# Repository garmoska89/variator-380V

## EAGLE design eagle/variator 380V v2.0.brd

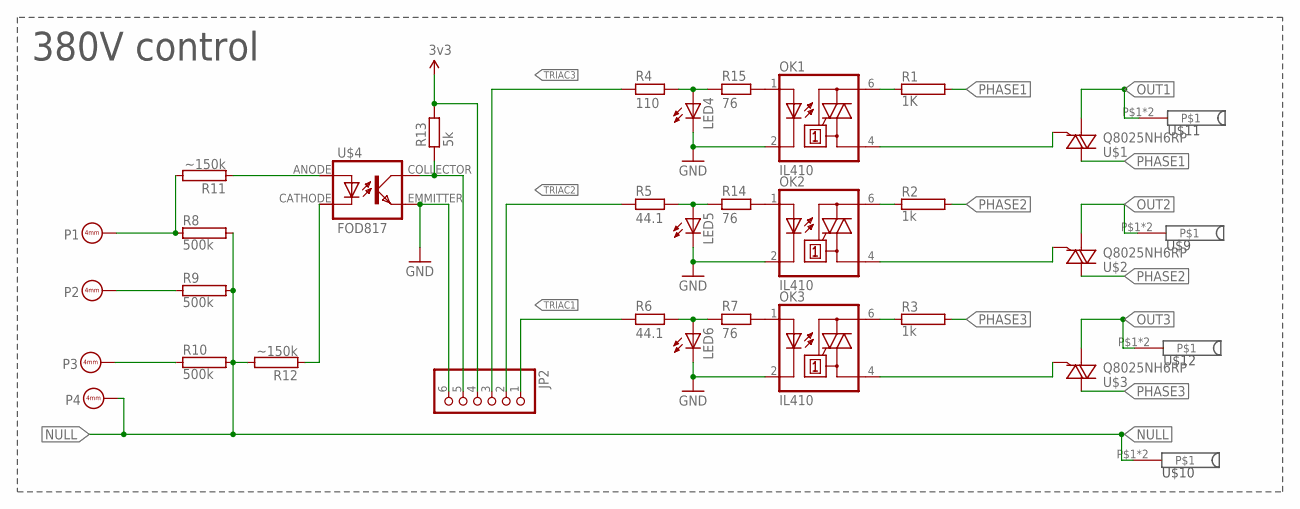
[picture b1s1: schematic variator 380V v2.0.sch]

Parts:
JP2: PINHD-1X6/90; 1X06/90
LED4, LED5, LED6: LED5MM
OK1, OK2, OK3: IL410; DIL06
P1, P2, P3, P4: BANANA
R1: 1K; HPS58
R2, R3: 1k; HPS58
R4: 110; 1206
R5, R6: 44.1; 1206
R7, R14, R15: 76; 1206
R8, R9, R10: 500k; HPS58
R11, R12: ~150k; HPS58
R13: 5k; 1206
U$1, U$2, U$3: Q8025NH6RP; TO-263
U$4: FOD817; FOD_4PIN
U$9, U$10, U$11, U$12: BANANA

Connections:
3V3: JP2.4, R13.2
GND: JP2.6, LED4.K (C), LED5.K (C), LED6.K (C), OK1.2 (C), OK2.2 (C), OK3.2 (C), U$4.EMMITTER (EMIT)
unnamed: OK2.4 (A1), U$2.G
unnamed: OK1.4 (A1), U$1.G
unnamed: OK3.4 (A1), U$3.G
unnamed: OK1.6 (A2), R1.1
unnamed: OK2.6 (A2), R2.1
unnamed: OK3.6 (A2), R3.1
unnamed: LED4.A, R4.2, R15.1
unnamed: OK3.1 (A), R7.2
unnamed: OK2.1 (A), R14.2
unnamed: LED5.A, R5.2, R14.1
unnamed: LED6.A, R6.2, R7.1
unnamed: OK1.1 (A), R15.2
unnamed: R12.1, U$4.CATHODE
unnamed: R11.1, U$4.ANODE
unnamed: JP2.5, R13.1, U$4.COLLECTOR (COL)
NULL: P4.P$1, R8.2, R9.2, R10.2, R12.2, U$10.P$1, U$10.P$2
OUT1: U$1.T1, U$11.P$1, U$11.P$2
OUT2: U$2.T1, U$9.P$1, U$9.P$2
OUT3: U$3.T1, U$12.P$1, U$12.P$2
PHASE1: P1.P$1, R1.2, R8.1, R11.2, U$1.T2
PHASE2: P2.P$1, R2.2, R9.1, U$2.T2
PHASE3: P3.P$1, R3.2, R10.1, U$3.T2
TRIAC1: JP2.1, R6.1
TRIAC2: JP2.2, R5.1
TRIAC3: JP2.3, R4.1

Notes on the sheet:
380V control

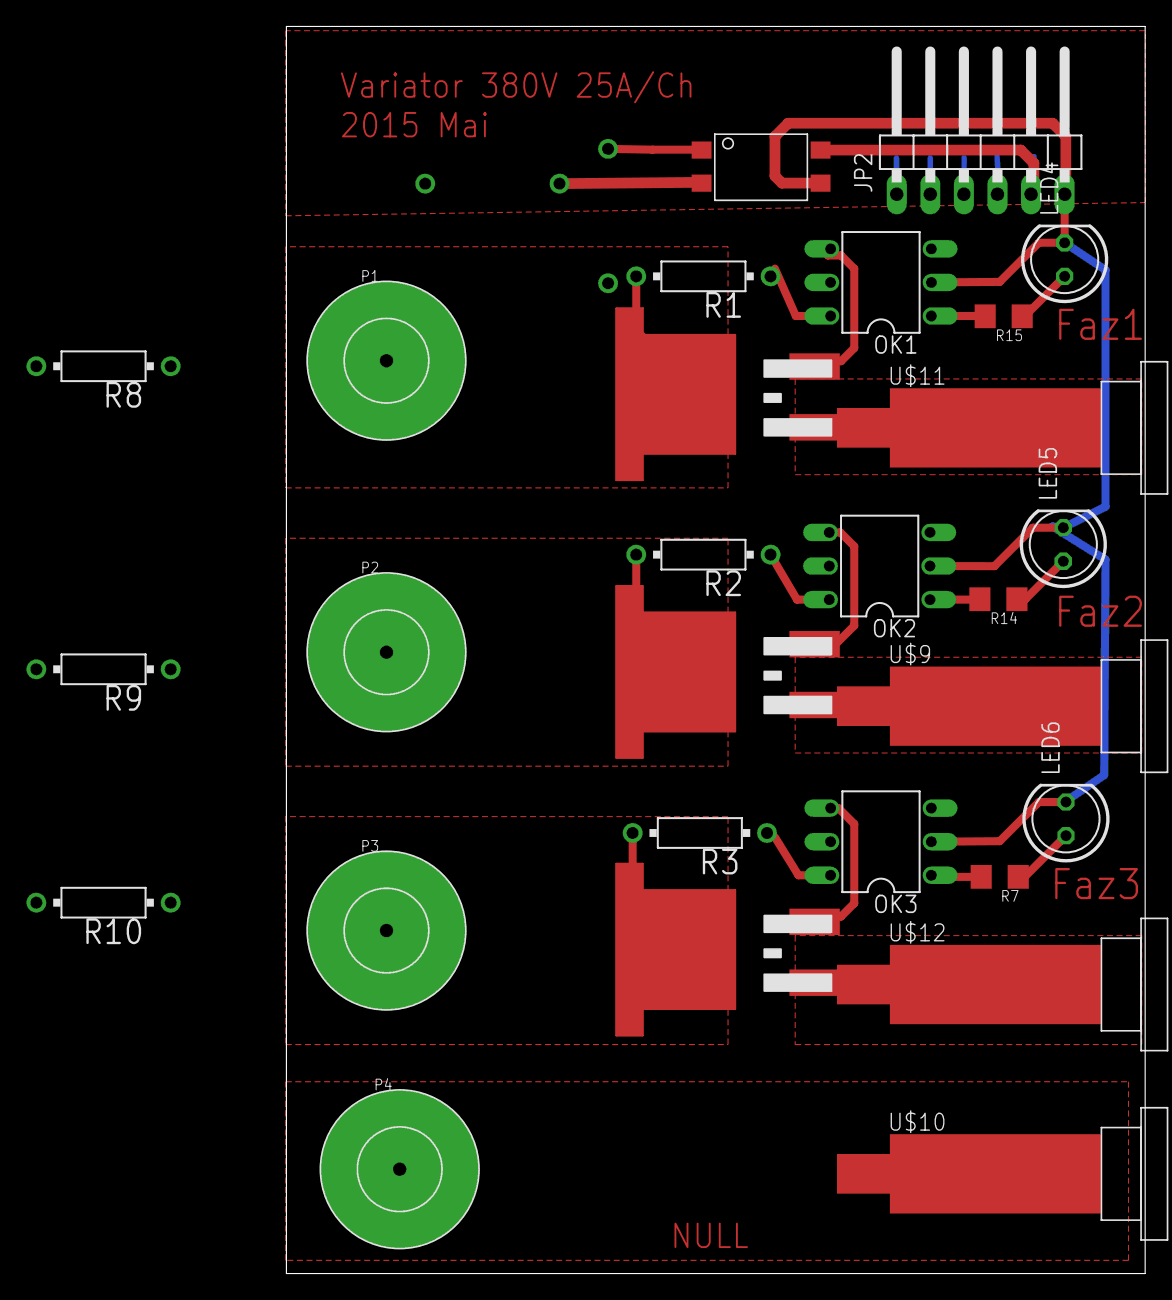
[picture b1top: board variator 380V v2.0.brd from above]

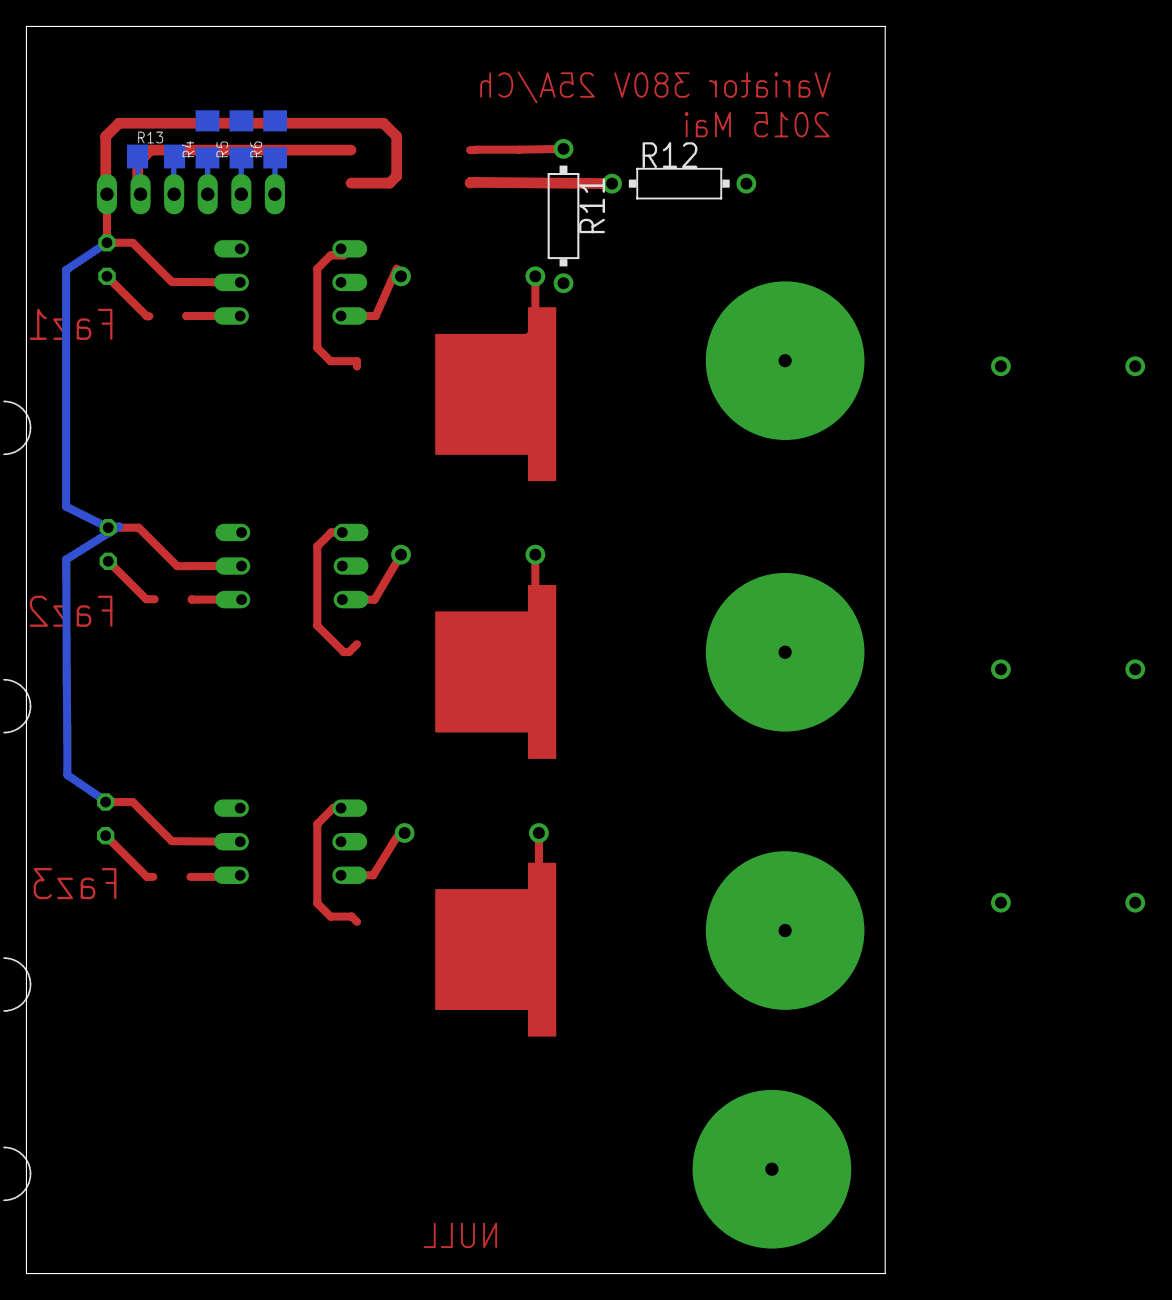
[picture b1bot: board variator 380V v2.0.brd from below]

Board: 2 copper layers, 65.0 x 94.3 mm, 34 parts (6 on the bottom side), 27 nets.

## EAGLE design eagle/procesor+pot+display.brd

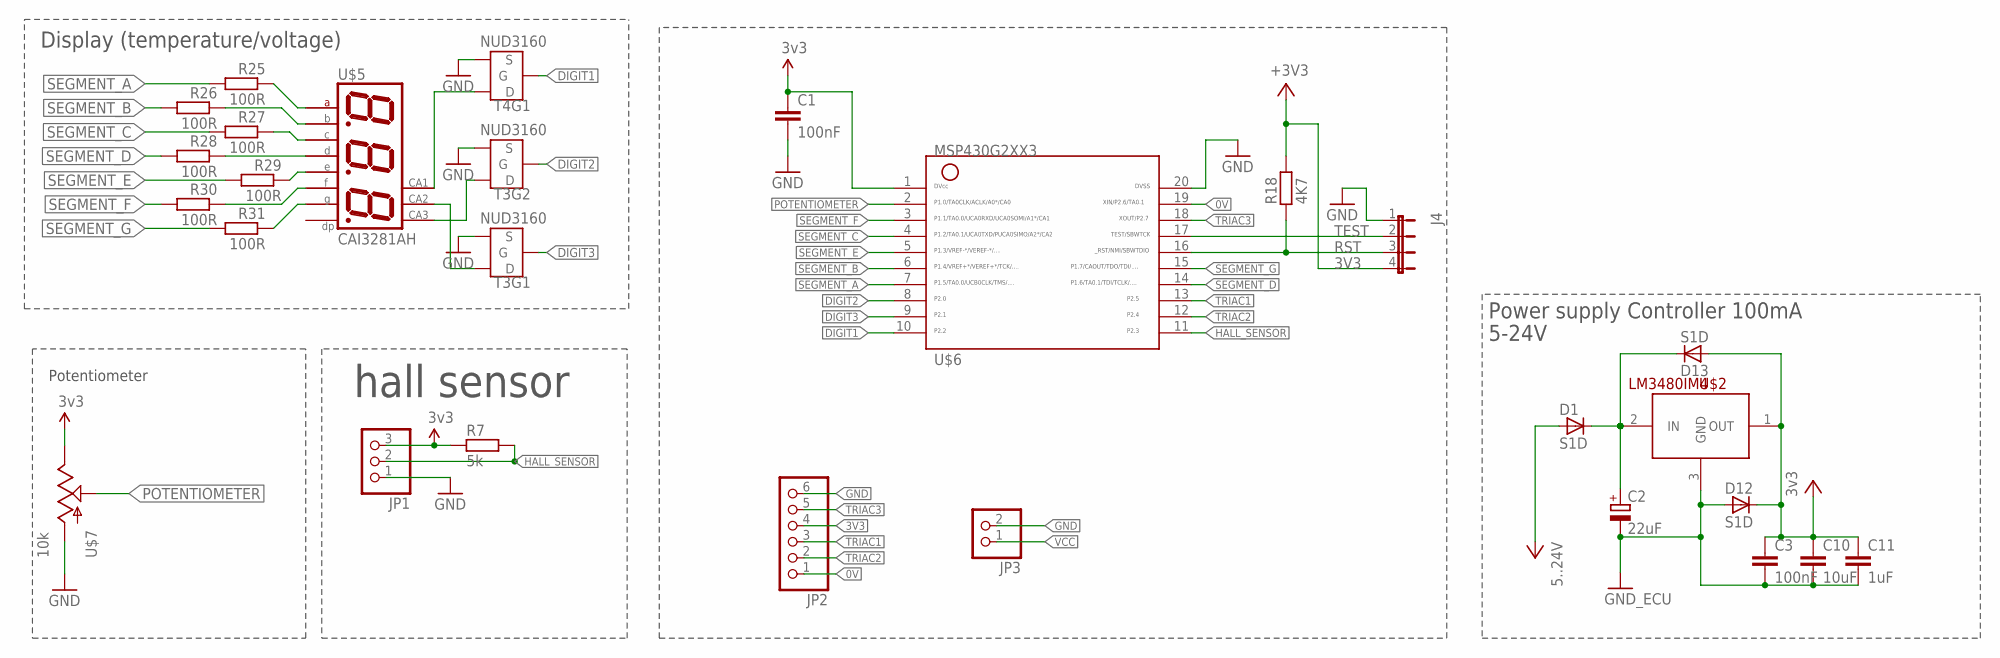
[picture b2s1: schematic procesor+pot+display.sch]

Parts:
C1: 100nF; 0603
C2: 22uF; C_EL_6.3X5.4
C3: 100nF; 1206
C10: 10uF; 1206
C11: 1uF; 1206
D1, D12, D13: S1D
J4: JP4
JP1: PINHD-1X3; 1X03
JP2: PINHD-1X6/90; 1X06/90
JP3: PINHD-1X2/90; 1X02/90
R7: 5k; 0603
R18: 4K7; 0805
R25, R26, R27, R28, R29, R30, R31: 100R; R0603
T3, T4: NUD3160; SOT23-6
U$2: LM3480IM4; SOT23-3
U$5: CAI3281AH; 7SEG_3DIGIT_10MMX30MM
U$6: G2XX3---PW20; PW20
U$7: 10k; POT

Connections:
0V: JP2.1, U$6.19
3V3: C1.1, C3.1, C10.1, C11.1, D12.C, D13.A, J4.4, JP1.3, JP2.4, R7.1, R18.2, U$2.1 (OUT), U$6.1, U$7.E@2 (E)
DIGIT1: T4.P$2 (G), U$6.10
DIGIT2: T3.P$5 (G), U$6.8
DIGIT3: T3.P$2 (G), U$6.9
GND: C1.2, C2.-, C3.2, C10.2, C11.2, D12.A, J4.1, JP1.1, JP2.6, JP3.2, T3.P$1 (S), T3.P$4 (S), T4.P$1 (S), U$2.3 (GND), U$6.20, U$7.E@1 (A)
HALL_SENSOR: JP1.2, R7.2, U$6.11
unnamed: T3.P$6 (D), U$5.P$8 (CA)
unnamed: C2.+, D1.C, D13.C, U$2.2 (IN)
unnamed: R31.1, U$5.P$3 (G)
unnamed: R30.1, U$5.P$5 (F)
unnamed: R29.1, U$5.P$9 (E)
unnamed: R28.1, U$5.P$2 (D)
unnamed: R27.1, U$5.P$4 (C)
unnamed: R26.1, U$5.P$6 (B)
unnamed: R25.1, U$5.P$10 (A)
unnamed: T3.P$3 (D), U$5.P$7 (CA)
unnamed: T4.P$6 (D), U$5.P$11 (CA)
POTENTIOMETER: U$6.2, U$7.WAND (S)
RST: J4.3, R18.1, U$6.16
SEGMENT_A: R25.2, U$6.7
SEGMENT_B: R26.2, U$6.6
SEGMENT_C: R27.2, U$6.4
SEGMENT_D: R28.2, U$6.14
SEGMENT_E: R29.2, U$6.5
SEGMENT_F: R30.2, U$6.3
SEGMENT_G: R31.2, U$6.15
TEST: J4.2, U$6.17
TRIAC1: JP2.3, U$6.13
TRIAC2: JP2.2, U$6.12
TRIAC3: JP2.5, U$6.18
VCC: D1.A, JP3.1

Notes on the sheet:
Display (temperature/voltage)
Potentiometer
hall sensor
Power supply Controller 100mA
5-24V

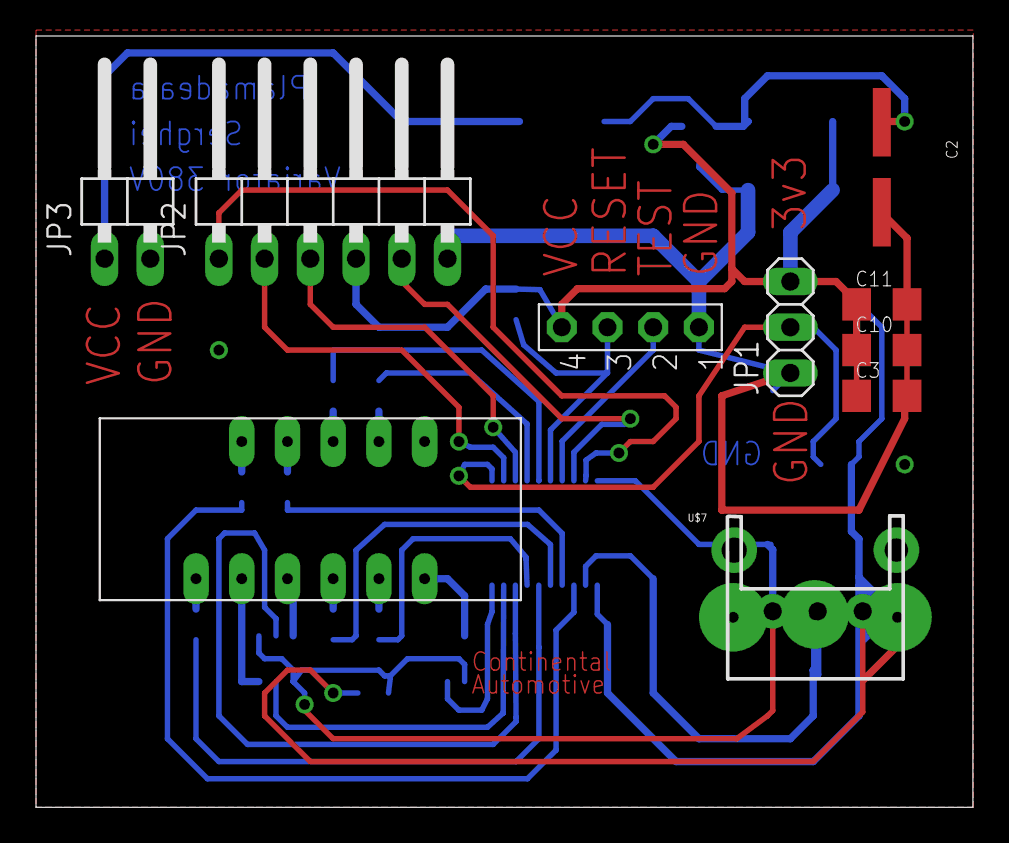
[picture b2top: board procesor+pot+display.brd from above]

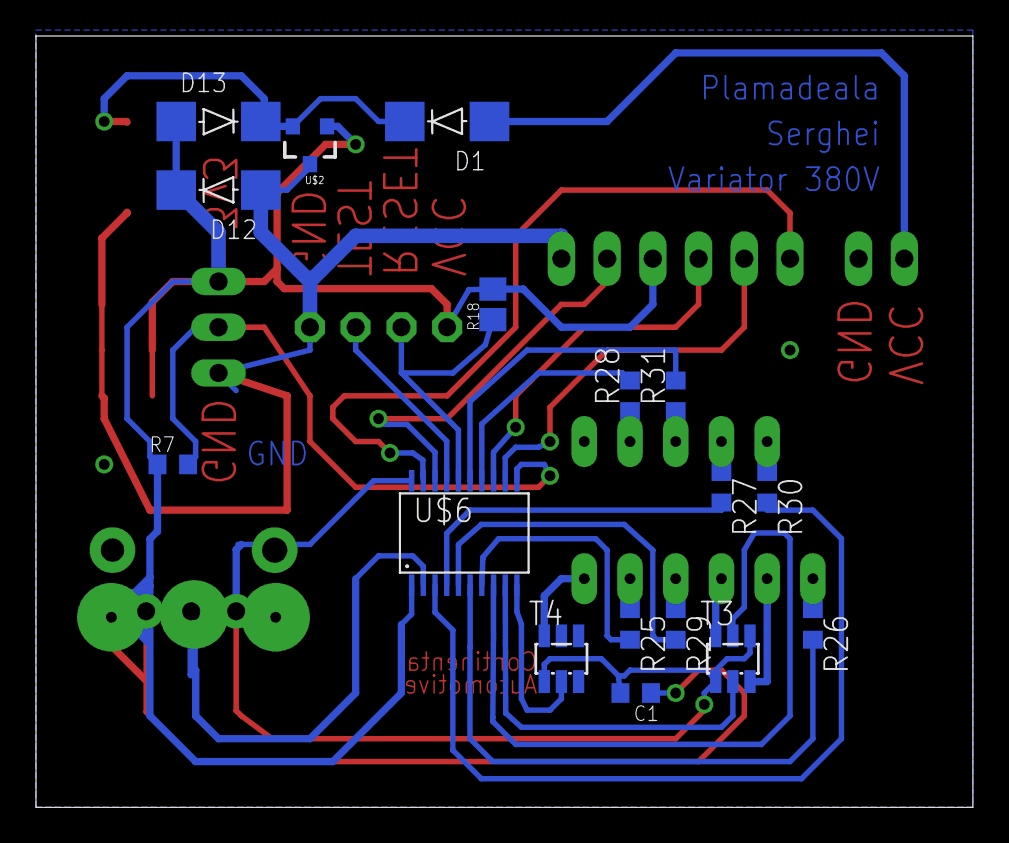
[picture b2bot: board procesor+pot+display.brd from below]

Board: 2 copper layers, 52.0 x 42.9 mm, 27 parts (17 on the bottom side), 32 nets.

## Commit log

2015-05-11 Correcting Triak supply
2015-05-11 pdf adding
2015-05-12 V 2.0 mai compacta
2015-05-12 modification on Microcontroller PCB
2015-05-16 Resistenta separate la fiecare led in parte. Led in parallel connection.
2015-05-26 code composer v2.0
2015-05-26 Capture timer first implementation
2015-05-28 adapting display method for number and letter need to be Test!!
2015-05-31 Implementare State machine. Implementare program cu hall sensor. Implementare program fara hall sensor.
2015-06-01 Ignore on start overflow, because Motor on start have very small rotation
2015-06-01 small modification in programWithHall
2015-06-01 Implementation correct dimmer and transition from HIGH to Normal Mode
2015-06-01 trecere lina cu sensor HAll de la HIGH la normal Mode si invers
2015-06-01 need verify to not accept spike between transition
2015-06-17 phase table.xlsx
2015-06-17 branch1
2015-07-03 test cut sinus
2015-07-04 correct state machine, implement potentiometer_rotation, add in state machine withoutHall_fault
2018-04-04 04.04.2018

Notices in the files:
parts and their libraries:
SparkFun-PowerIC: Licensing: Creative Commons ShareAlike 4.0 International - https://creativecommons.org/licenses/by-sa/4.0
